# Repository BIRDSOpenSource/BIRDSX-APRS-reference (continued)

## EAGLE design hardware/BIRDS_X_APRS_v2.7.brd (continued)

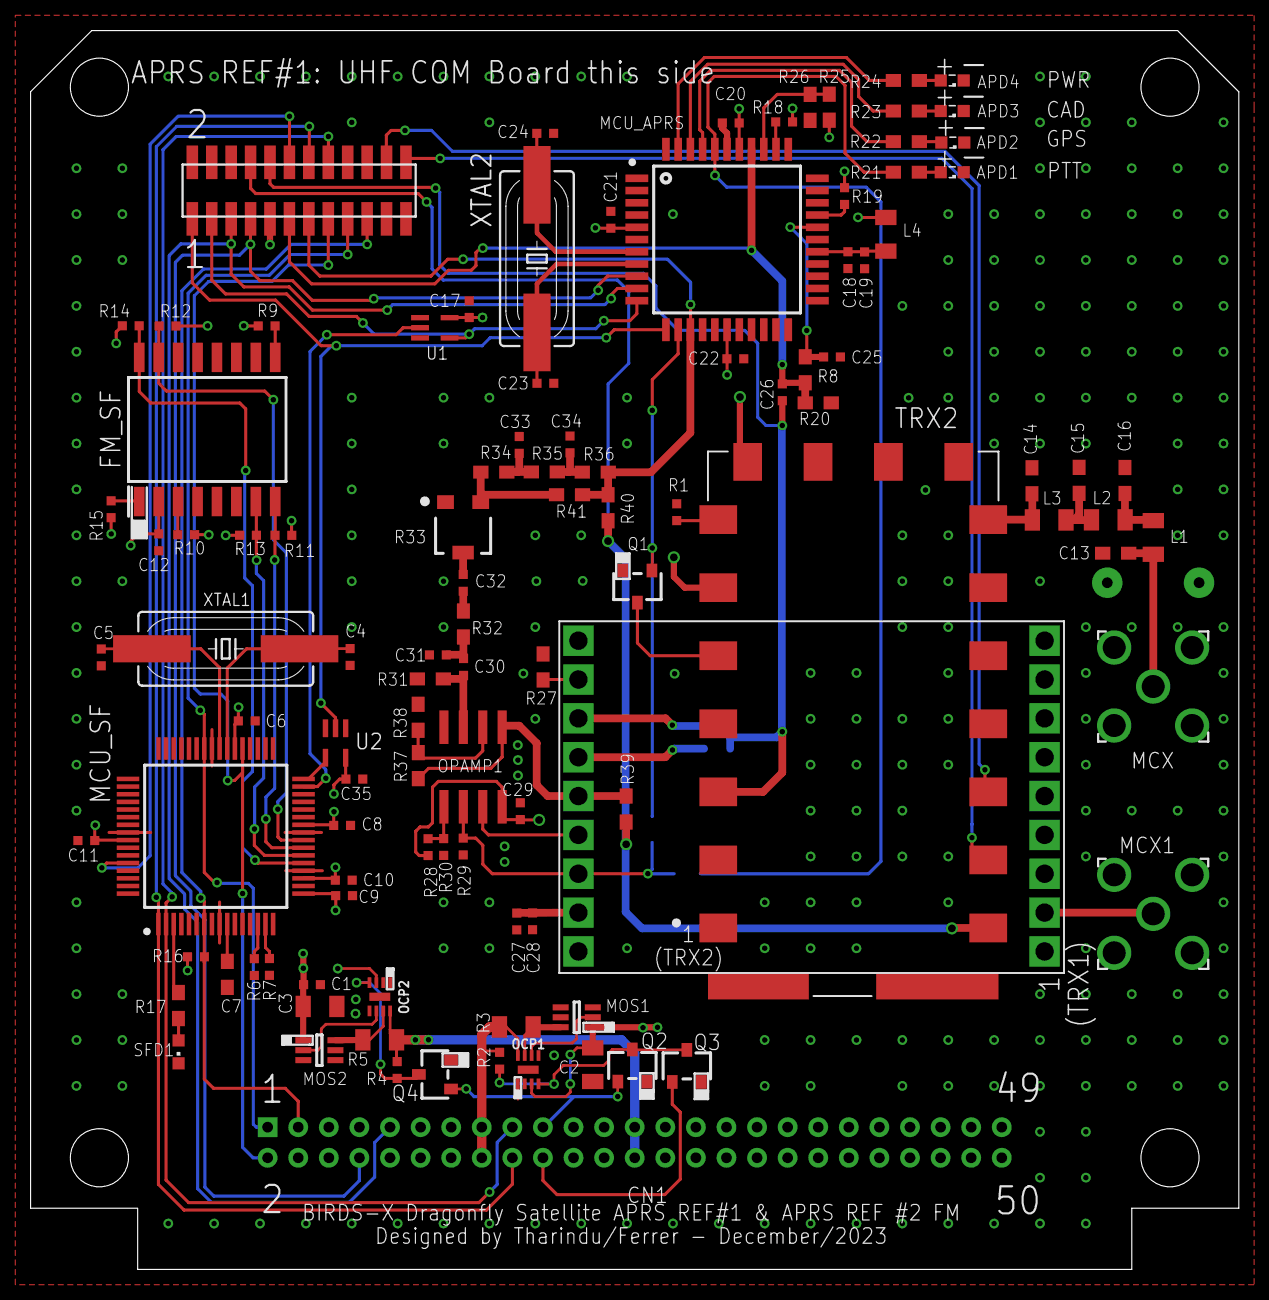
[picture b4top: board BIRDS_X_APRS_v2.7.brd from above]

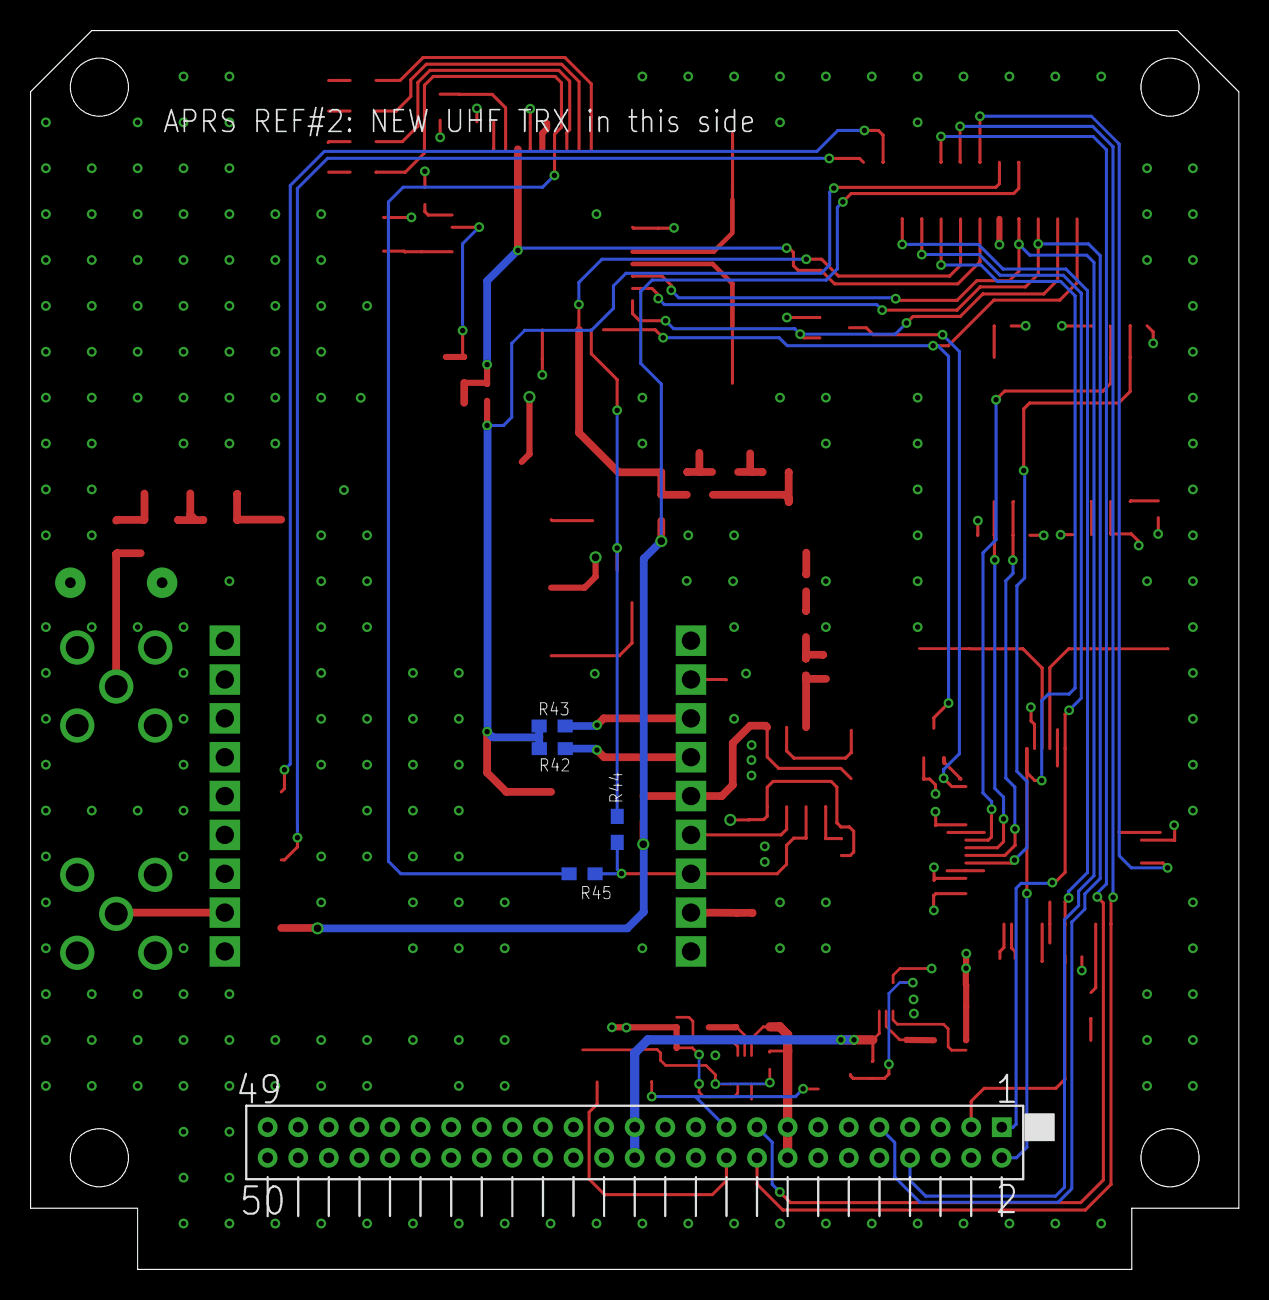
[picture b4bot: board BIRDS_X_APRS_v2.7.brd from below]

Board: 4 copper layers, 79.0 x 81.0 mm, 111 parts (4 on the bottom side), 82 nets.

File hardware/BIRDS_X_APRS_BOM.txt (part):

Part     Value                 Device                Package                 Description                                                                                                                    3D_PACKAGE ALLIED_NUMBER ALLIED_PRICE-STOCK                                                             AVAILABILITY CHECK_PRICES                                                                     DESCRIPTION                                                                                                                    DIGI-KEY_PART_NUMBER DIGI-KEY_PURCHASE_URL                                                                                                                                HEIGHT MANUFACTURER_NAME MANUFACTURER_PART_NUMBER MF                 MOUSER_PART_NUMBER   MOUSER_PRICE-STOCK                                                       MP             MPN OC_FARNELL OC_NEWARK OTHER_PART_NUMBER PACKAGE                    POPULARITY PRICE PURCHASE-URL                                                    RS_PART_NUMBER RS_PRICE-STOCK                                 SNAPEDA_LINK                                                                      SUPPLIER_NAME
APD1                           LEDSML0603            SML0603                 LED                                                                                                                                                                                                                                                                                                                                                                                                                                                                                                                                                                                                                                                                                                                                                                                                                                                                                                   17                                                                                                                                                                                                                                            
APD2                           LEDSML0603            SML0603                 LED                                                                                                                                                                                                                                                                                                                                                                                                                                                                                                                                                                                                                                                                                                                                                                                                                                                                                                   17                                                                                                                                                                                                                                            
APD3                           LEDSML0603            SML0603                 LED                                                                                                                                                                                                                                                                                                                                                                                                                                                                                                                                                                                                                                                                                                                                                                                                                                                                                                   17                                                                                                                                                                                                                                            
APD4                           LEDSML0603            SML0603                 LED                                                                                                                                                                                                                                                                                                                                                                                                                                                                                                                                                                                                                                                                                                                                                                                                                                                                                                   17                                                                                                                                                                                                                                            
C1       0.1uF                 CAPACITOR             M(1005)_US(0402)                                                                                                                                                                                                                                                                                                                                                                                                                                                                                                                                                                                                                                                                                                                                                                                                                                                                                                                                                                                                                                                                                                                                                            
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
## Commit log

2024-11-08 Create 01
